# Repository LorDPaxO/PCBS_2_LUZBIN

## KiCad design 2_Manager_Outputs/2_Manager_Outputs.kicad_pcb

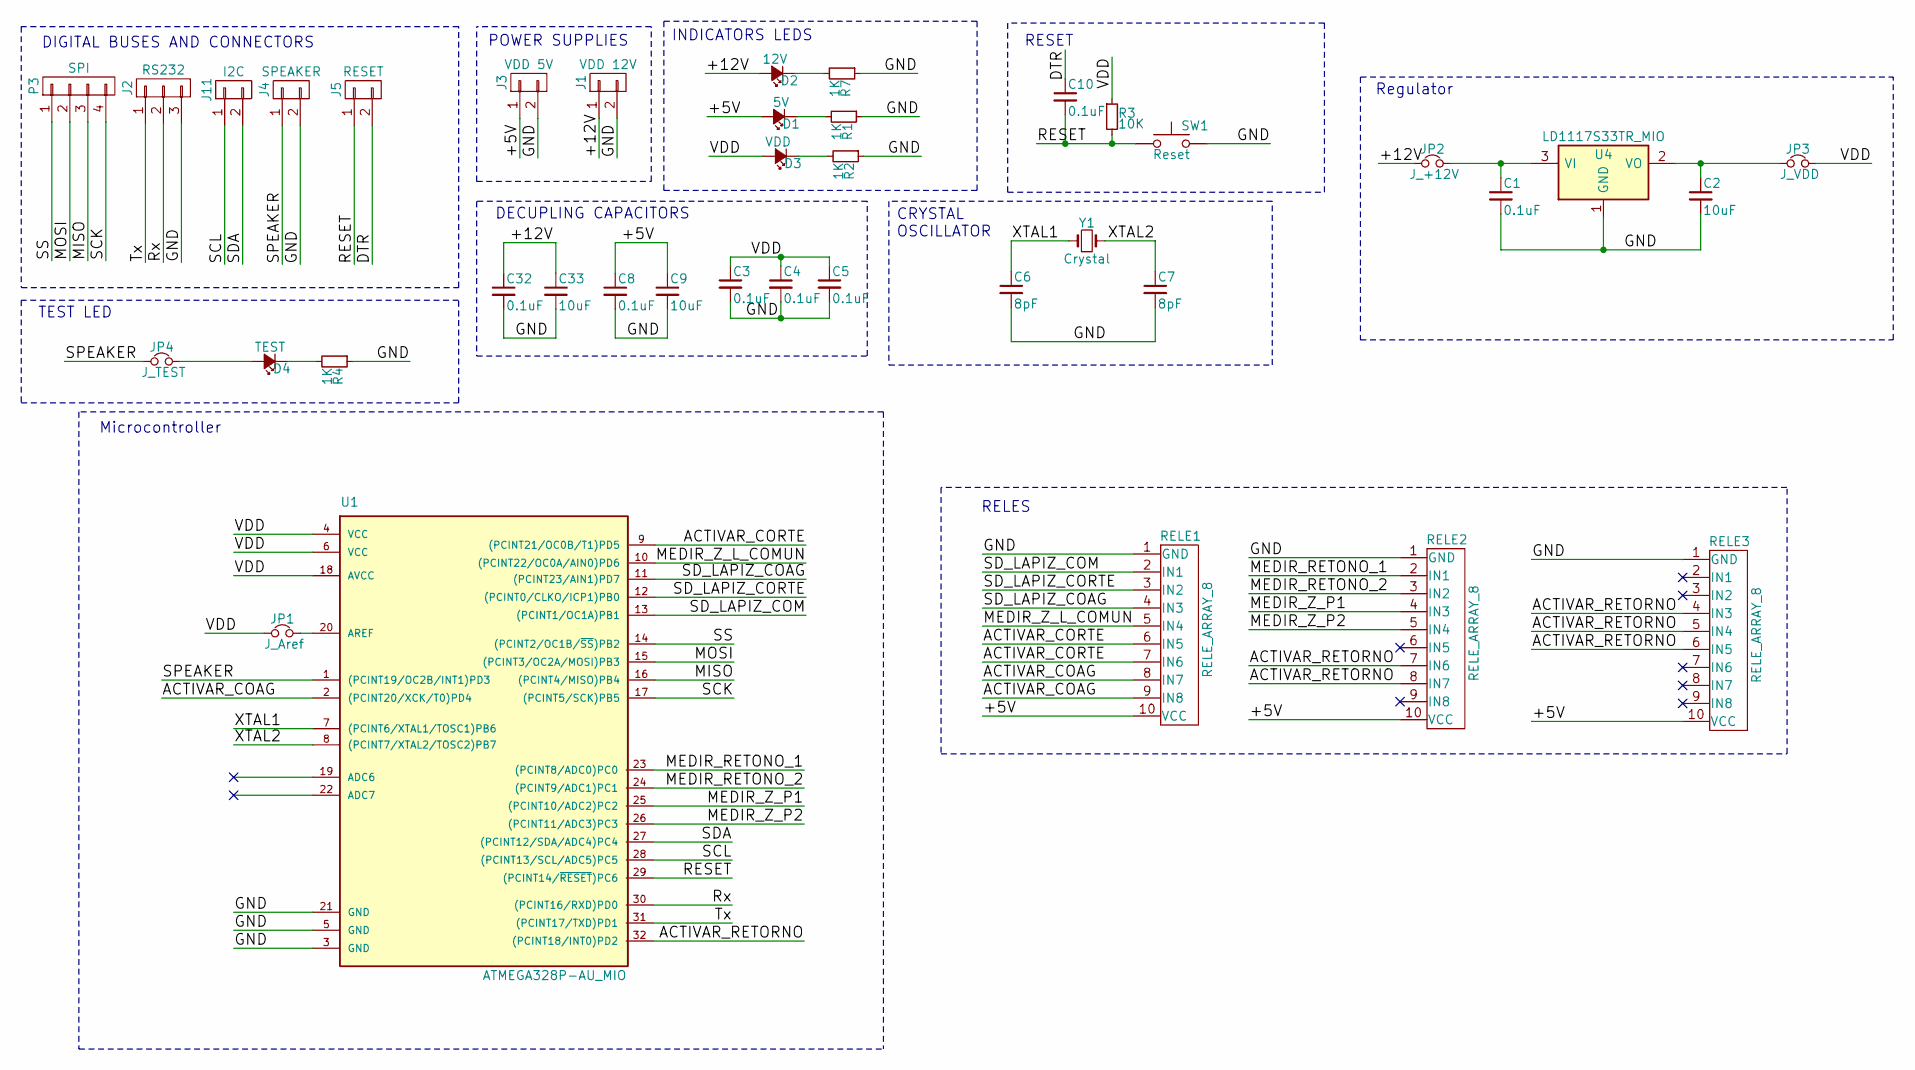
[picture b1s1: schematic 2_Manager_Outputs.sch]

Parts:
C1, C3, C4, C5, C10: 0.1uF; R_0805_HandSoldering; Digi-Key Part Number 478-1395-2-ND
C2: 10uF; R_0805_HandSoldering
C6, C7: 8pF; C_0402
C8, C32: 0.1uF; C_0805_HandSoldering; Digi-Key Part Number 478-1395-2-ND
C9, C33: 10uF; C_0805_HandSoldering
D1: 5V; R_0805_HandSoldering; Digi-Key Part Number 475-1410-2-ND
D2: 12V; R_0805_HandSoldering; Digi-Key Part Number 475-1410-2-ND
D3: VDD; R_0805_HandSoldering; Digi-Key Part Number 475-1410-2-ND
D4: TEST; R_0805_HandSoldering; Digi-Key Part Number 475-1410-2-ND
J1: VDD 12V; SUPPLY_12V
J2: RS232
J3: VDD 5V; SUPPLY_5V
J4: SPEAKER; Socket_Strip_Straight_1x02
J5: RESET; RESET_CONNECTOR
J11: I2C; I2C_2X4
JP1: J_Aref; R_0805_HandSoldering
JP2: J_+12V; Socket_Strip_Straight_1x02
JP3: J_VDD; Socket_Strip_Straight_1x02
JP4: J_TEST; Pin_Header_Straight_1x02
P3: SPI; SPI_CONNECTOR
R1, R2, R4, R7: 1K; R_0805_HandSoldering
R3: 10K; R_0805_HandSoldering
RELE1, RELE3: RELE_ARRAY_8; Socket_Strip_Straight_2x10_Mio_2
RELE2: RELE_ARRAY_8; Socket_Strip_Straight_2x10_Mio
SW1: Reset; KPT_1187B
U1: ATMEGA328P-AU_MIO; TQFP-32_7x7mm_Pitch0.8mm
U4: LD1117S33TR_MIO; SOT-223
Y1: Crystal; Crystal_SMD_XRCHA_Murata_Serie_W2,5mm_L2,0mm

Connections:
/+5V: C8.1, C9.1, D1.2 (A), J3.1, RELE1.10 (VCC), RELE2.10 (VCC), RELE3.10 (VCC)
/+12V: C32.1, C33.1, D2.2 (A), J1.1, JP2.1
/ACTIVAR_COAG: RELE1.8 (IN7), RELE1.9 (IN8), U1.2 ((PCINT20/XCK/T0)PD4)
/ACTIVAR_CORTE: RELE1.6 (IN5), RELE1.7 (IN6), U1.9 ((PCINT21/OC0B/T1)PD5)
/ACTIVAR_RETORNO: RELE2.7 (IN6), RELE2.8 (IN7), RELE3.4 (IN3), RELE3.5 (IN4), RELE3.6 (IN5), U1.32 ((PCINT18/INT0)PD2)
/DTR: C10.1, J5.2
/GND: C1.2, C2.2, C3.2, C4.2, C5.2, C6.2, C7.2, C8.2, C9.2, C32.2, C33.2, J1.2, J2.3, J3.2, J4.2, R1.1, R2.1, R4.1, R7.1, RELE1.1 (GND), RELE2.1 (GND), RELE3.1 (GND), SW1.2, U1.3 (GND), U1.5 (GND), U1.21 (GND), U4.1 (GND)
/MEDIR_RETONO_1: RELE2.2 (IN1), U1.23 ((PCINT8/ADC0)PC0)
/MEDIR_RETONO_2: RELE2.3 (IN2), U1.24 ((PCINT9/ADC1)PC1)
/MEDIR_Z_L_COMUN: RELE1.5 (IN4), U1.10 ((PCINT22/OC0A/AIN0)PD6)
/MEDIR_Z_P1: RELE2.4 (IN3), U1.25 ((PCINT10/ADC2)PC2)
/MEDIR_Z_P2: RELE2.5 (IN4), U1.26 ((PCINT11/ADC3)PC3)
/MISO: P3.3, U1.16 ((PCINT4/MISO)PB4)
/MOSI: P3.2, U1.15 ((PCINT3/OC2A/MOSI)PB3)
/RESET: C10.2, J5.1, R3.2, SW1.1, U1.29 ((PCINT14/~RESET~)PC6)
/Rx: J2.2, U1.30 ((PCINT16/RXD)PD0)
/SCK: P3.4, U1.17 ((PCINT5/SCK)PB5)
/SCL: J11.1, U1.28 ((PCINT13/SCL/ADC5)PC5)
/SDA: J11.2, U1.27 ((PCINT12/SDA/ADC4)PC4)
/SD_LAPIZ_COAG: RELE1.4 (IN3), U1.11 ((PCINT23/AIN1)PD7)
/SD_LAPIZ_COM: RELE1.2 (IN1), U1.13 ((PCINT1/OC1A)PB1)
/SD_LAPIZ_CORTE: RELE1.3 (IN2), U1.12 ((PCINT0/CLKO/ICP1)PB0)
/SPEAKER: J4.1, JP4.1, U1.1 ((PCINT19/OC2B/INT1)PD3)
/SS: P3.1, U1.14 ((PCINT2/OC1B/~SS~)PB2)
/Tx: J2.1, U1.31 ((PCINT17/TXD)PD1)
/VDD: C3.1, C4.1, C5.1, D3.2 (A), JP1.1, JP3.2, R3.1, U1.4 (VCC), U1.6 (VCC), U1.18 (AVCC)
/XTAL1: C6.1, U1.7 ((PCINT6/XTAL1/TOSC1)PB6), Y1.1
/XTAL2: C7.1, U1.8 ((PCINT7/XTAL2/TOSC2)PB7), Y1.2
unnamed: C1.1, JP2.2, U4.3 (VI)
unnamed: C2.1, JP3.1, U4.2 (VO)
unnamed: D1.1 (K), R1.2
unnamed: D2.1 (K), R7.2
unnamed: D3.1 (K), R2.2
unnamed: D4.1 (K), R4.2
unnamed: D4.2 (A), JP4.2
unnamed: JP1.2, U1.20 (AREF)

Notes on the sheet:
DIGITAL BUSES AND CONNECTORS
POWER SUPPLIES
Regulator
RELES
RESET
CRYSTAL OSCILLATOR
DECUPLING CAPACITORS
INDICATORS LEDS
Microcontroller
TEST LED

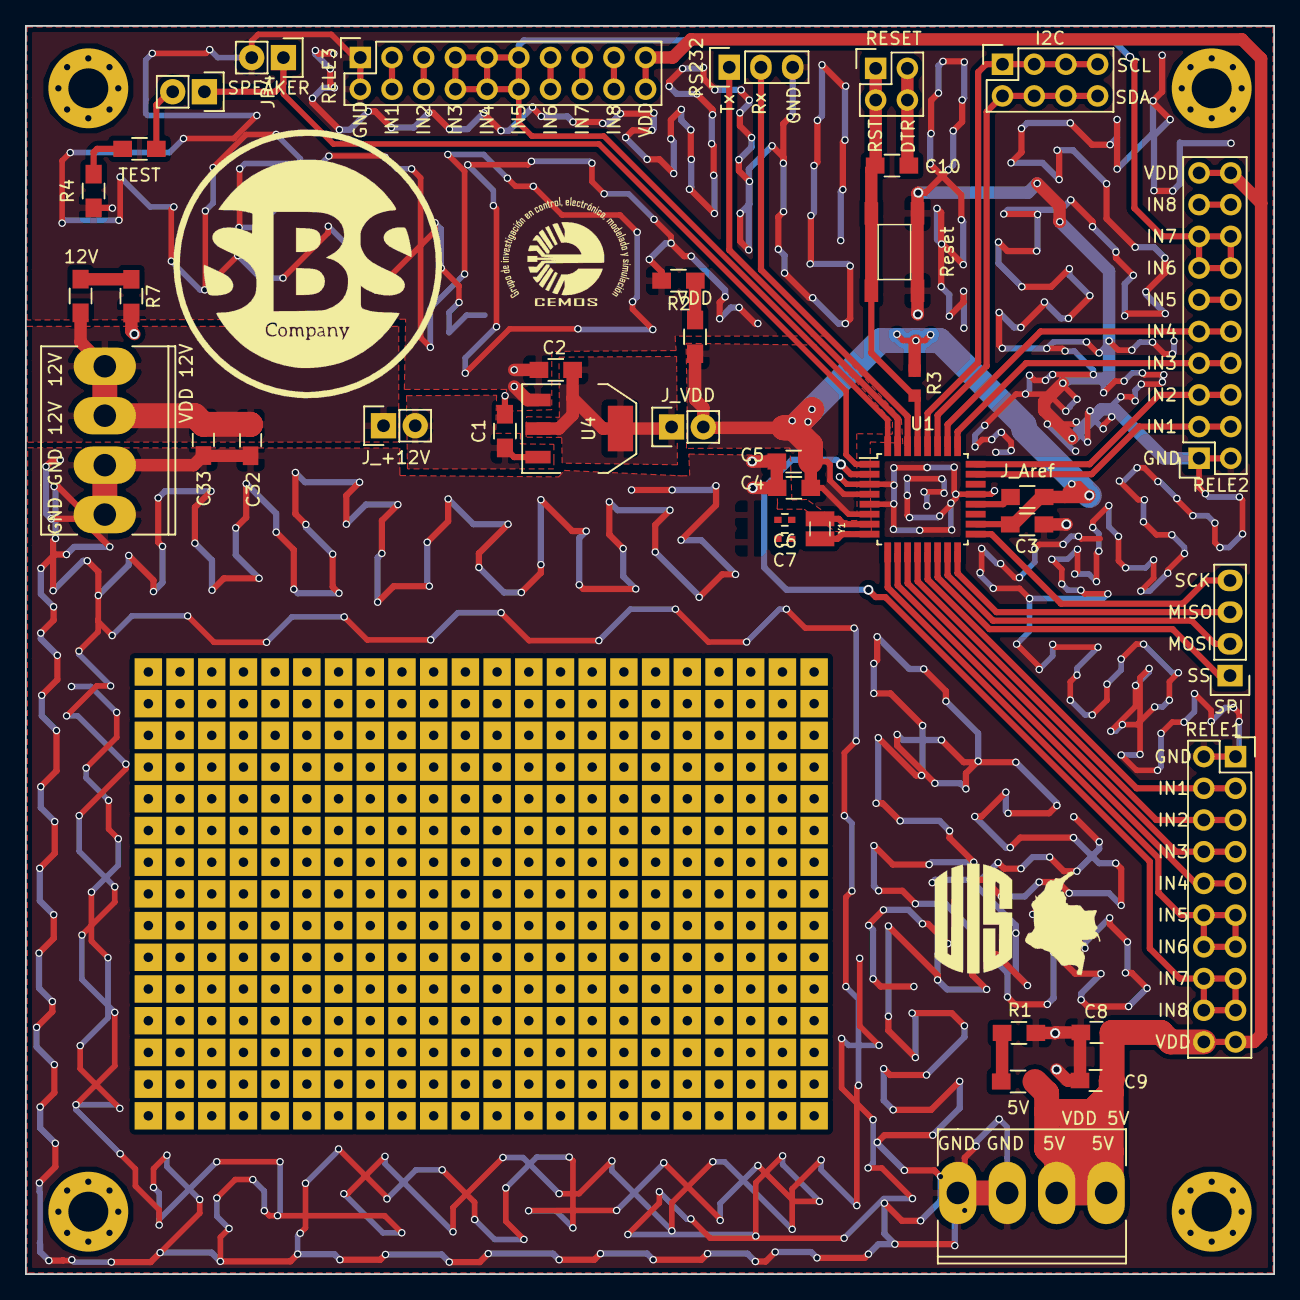
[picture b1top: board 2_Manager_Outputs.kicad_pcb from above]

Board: 2 copper layers, 100.0 x 100.0 mm, 39 parts (0 on the bottom side), 36 nets.

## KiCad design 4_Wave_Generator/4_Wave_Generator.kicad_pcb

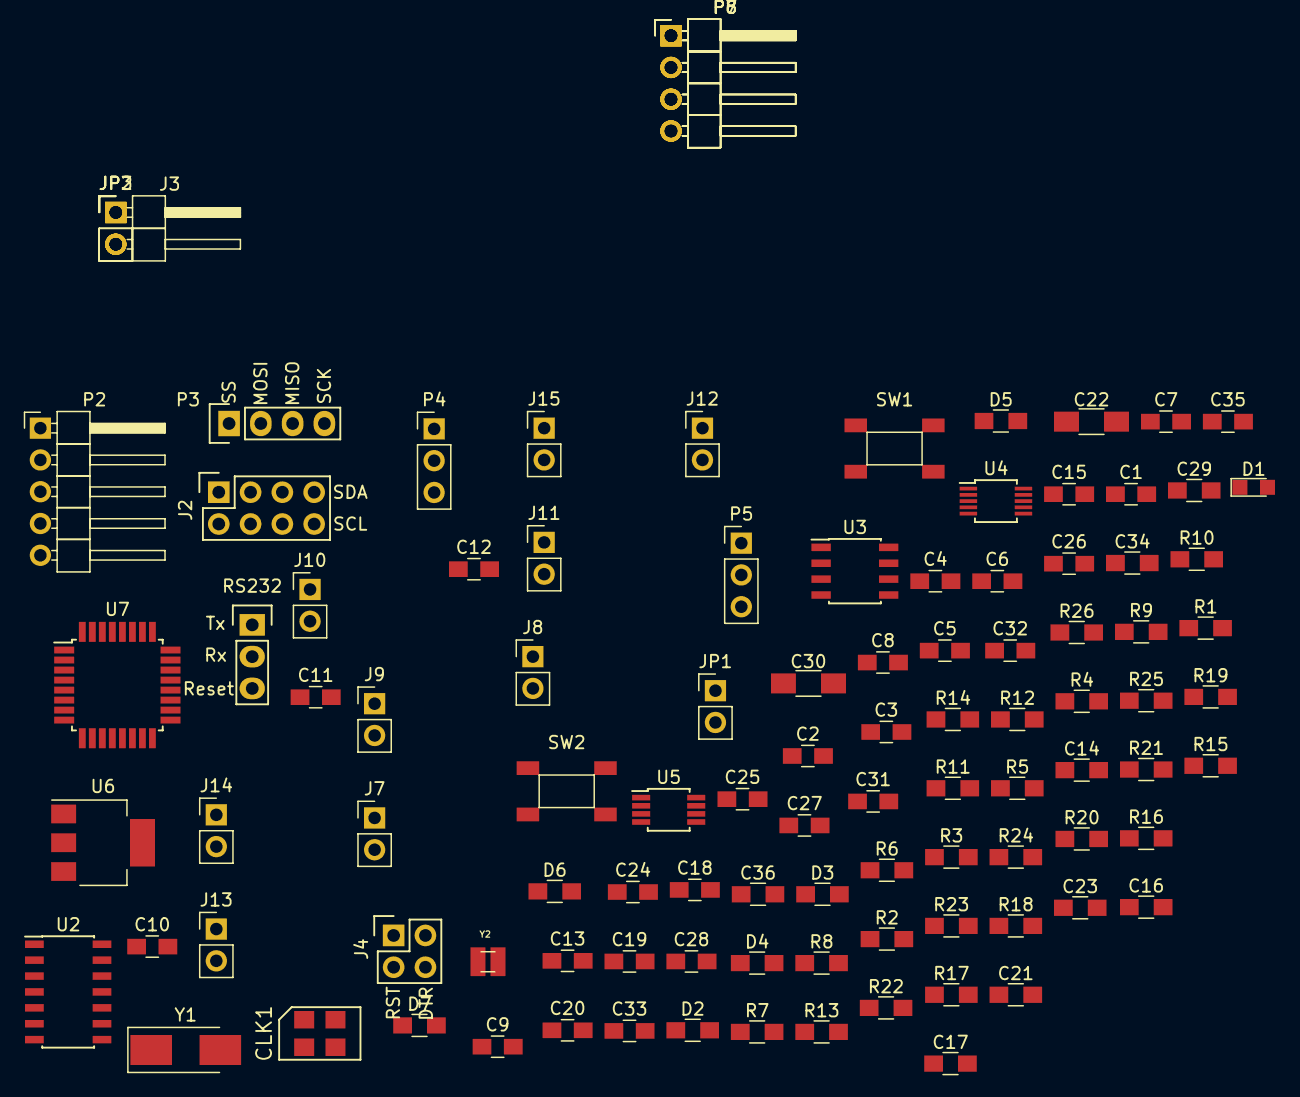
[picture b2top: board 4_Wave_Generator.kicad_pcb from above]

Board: 2 copper layers, 103 parts (0 on the bottom side), 65 nets, no tracks yet.

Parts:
C1: 1nF; C_0805_HandSoldering
C2, C3: 0.33uF; C_0805_HandSoldering
C4: 10nF; C_0805_HandSoldering
C5: 1.5nF; C_0805_HandSoldering
C6, C7, C8, C10, C11, C13, C20, C24, C26, C27, C28, C31, C35: 0.1uF; C_0805_HandSoldering
C9, C12, C15, C25: 10uF; C_0805_HandSoldering
C14, C16, C17, C23, C34: 0.1uF; R_0805_HandSoldering
C18, C19: 22pF; C_0805_HandSoldering
C21, C29: 8pF; R_0805_HandSoldering
C22, C30: 10uF; C_1206_HandSoldering
C32: 0.01uF; C_0805_HandSoldering
C33: 20pF; C_0805_HandSoldering
C36: 10uF; R_0805_HandSoldering
CLK1: KC5032A; KC5032A_Foot_Print
D1: LED; LED_0805
D2: 12V; R_0805_HandSoldering
D3: 5V; R_0805_HandSoldering
D4: VDD; R_0805_HandSoldering
D5, D6, D7: Led_0805; R_0805_HandSoldering
J1: RS232
J2: I2C; I2C_2X4
J3: SPEAKER; Pin_Header_Angled_1x02_Pitch2.54mm
J4: RESET; RESET_CONNECTOR
J7, J8, J9, J10, J11, J12, J13, J14, J15: Jumper; Pin_Header_Straight_1x02_Pitch2.54mm
JP1: PASO_A/D; Pin_Header_Straight_1x02_Pitch2.54mm
JP2: J_+12V; Pin_Header_Straight_1x02_Pitch2.54mm
JP3: J_VDD; Pin_Header_Straight_1x02_Pitch2.54mm
P2: PIC_PROGRAMER; Pin_Header_Angled_1x05_Pitch2.54mm
P3: SPI; SPI_CONNECTOR
P4: AD8232_CONTROL; Pin_Header_Straight_1x03_Pitch2.54mm
P5: PIC_OUTPUTS; Pin_Header_Straight_1x03_Pitch2.54mm
P6, P7: CONN_01X04; Pin_Header_Angled_1x04_Pitch2.54mm
P8: MCLK_EXTERNAL; Pin_Header_Angled_1x04_Pitch2.54mm
R1, R4, R8, R10, R12, R14: 10M; R_0805_HandSoldering
R2, R17, R18, R19, R20, R22, R23, R24: 1K; R_0805_HandSoldering
R3: 360K; R_0805_HandSoldering
R5, R6: 180K; R_0805_HandSoldering
R7: 1.4M; R_0805_HandSoldering
R9, R11, R15: 1M; R_0805_HandSoldering
R13: 100K; R_0805_HandSoldering
R16, R21, R25, R26: 10K; R_0805_HandSoldering
SW1: SW_Push; KPT_1187B
SW2: RESET_PIC; KPT_1187B
U2: PIC16F688; SOIC-14_3.9x8.7mm_Pitch1.27mm
U3: AD8421; SOIC-8_3.9x4.9mm_Pitch1.27mm
U4: AD9833; MSOP-10_3x3mm_Pitch0.5mm
U5: ADG819; MSOP-8_3x3mm_Pitch0.65mm
U6: LD1117S33TR_MIO; SOT-223
U7: ATMEGA328P-AU_MIO; TQFP-32_7x7mm_Pitch0.8mm
Y1: Crystal_8MHz; Crystal_SMD_Abracon_ABM3-2pin_5.0x3.2mm_HandSoldering
Y2: Crystal; Crystal_SMD_XRCHA_Murata_Serie_W2,5mm_L2,0mm

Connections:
+vs: C7.2, R12.1
/+5V: C11.1, C12.1
/+12V: C8.1, C9.1, C28.2, C30.2, D2.2, D7.2, JP2.1, P7.1, P7.2, U3.8
/-12V: C22.2, C24.1, P7.3, P7.4, R20.1, R24.1, U3.5
/ADC: C10.1, R17.1, U2.11
/BASE_WAVE: J13.1, U5.8
/DTR: C23.1, J4.2
/GND: C6.2, C7.1, C8.2, C9.2, C10.2, C11.2, C12.2, C13.2, C14.2, C15.2, C16.2, C17.2, C18.2, C19.2, C20.2, C21.2, C22.1, C24.2, C25.2, C26.2, C27.2, C28.1, C29.2, C30.1, C31.2, C33.2, C34.2, C35.1, C36.2, CLK1.2, D1.1, D4.2, D5.2, J1.3, J3.2, J12.2, P2.3, P5.1, P6.3, P6.4, R14.2, R18.1, R19.1, R21.1, R22.1, R23.1, SW1.2, SW2.1, U2.14, U3.1, U4.4, U4.9, U5.2, U5.3, U6.1, U7.3, U7.5, U7.21
/IAOUT: R9.1, R10.1
/ICSPCLK: P2.5, U2.12
/ICSPDAT: P2.4, U2.13
/MCLK_DDS_1: CLK1.3, J11.2
/MCLR/Vpp: P2.1, R26.2, SW2.2, U2.4
/MISO: P3.3, U7.16
/MOSI: P3.2, U7.15
/OPAMP+: C4.2, R11.1
/OUT_ANALOG: C5.1, JP1.1, R2.1, R15.2
/O_DIG1: P5.2, U2.8
/O_DIG2: P5.3, U2.7
/REFIN: C6.1, R12.2, R14.1
/REFOUT: C2.1, C4.1, R13.1
/RESET: C23.2, J4.1, R25.2, SW1.1, U7.29
/RLD: C1.2, R3.2
/Rx: J1.2, U7.30
/SCK: P3.4, U7.17
/SCL: J2.1, U7.28
/SDA: J2.2, U7.27
/SDN: P4.1, R16.1
/SS: P3.1, U7.14
/SW: C2.2, R7.2
/Tx: J1.1, U7.31
/VDD: C14.1, C16.1, C17.1, C20.1, C27.1, C31.1, C32.1, C35.2, CLK1.4, D3.2, J7.2, JP3.2, P2.2, R1.1, R4.1, R16.2, R25.1, R26.1, U2.1, U4.2, U5.4, U7.4, U7.6, U7.18
/VDD_F: C13.1, C15.1, D6.2
/WAVE_DDS_1: J14.1, U3.4
/XTAL1: C21.1, U7.7, Y2.1
/XTAL2: C29.1, U7.8, Y2.2
LA: R4.2, R5.1
unnamed: C3.1, R8.2
unnamed: C5.2, R9.2, R11.2
unnamed: C18.1, U2.2, Y1.1
unnamed: C19.1, U2.3, Y1.2
unnamed: C25.1, C26.1, U4.3
unnamed: C32.2, U4.1
unnamed: C33.1, J14.2, U4.10
unnamed: C34.1, JP2.2, U6.3
unnamed: C36.1, JP3.1, U6.2
unnamed: CLK1.1, J7.1, R21.2
unnamed: D1.2, R2.2
unnamed: D2.1, R18.2
unnamed: D3.1, R19.2
unnamed: D4.1, R20.2
unnamed: D5.1, R24.2
unnamed: D6.1, R22.2
unnamed: D7.1, R23.2
unnamed: J8.1, U3.2
unnamed: J9.1, U3.3
unnamed: J10.1, J11.1, U4.5
unnamed: J10.2, P8.1
unnamed: J12.1, U3.6
unnamed: J13.2, U3.7
unnamed: J15.2, U5.1
unnamed: JP1.2, R17.2
unnamed: R7.1, R8.1, R10.2
unnamed: R13.2, R15.1
RA: R1.2, R6.1

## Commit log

2017-09-30 :tada: Added .gitattributes & .gitignore files
2017-09-30 //
    //
2017-09-30 //
    Plantilla para hacer tanto la pcb de manager output como la pcb de wave
    generator// Separar el diseño en dos y empezar a trabajar por aparte
    cada pcb
2017-10-01 //
    Dejo plantilla para iniciar cualquiera de las dos pcbs
2017-10-01 //
    Dejo el esquematico solo con las cosas del manager Outut
2017-10-03 V1.0
    //HAGO GERBERS PARA VERIFICAR CUALQUIER ERROR.
2017-12-05 Revert "//"
    This reverts commit a491b2ffacc572f737e67cceefcc72cf1d6daf07.
